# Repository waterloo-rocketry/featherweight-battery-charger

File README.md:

# featherweight-battery-charger

- add grounds
- when your chip suddenly draws a lot of power, it gets a big change in current which is a problem: in those moments, voltage is irregular. so the point of decoupling capacitor is to store charge
- in general, depends on pin/chip, datasheet will give recommended or calculate it yourself :(
- change resistor value (?)
- buck converter -> 12v to 5v (do this cuz it's step down standard), we probably need to design it (we gotta buy buck converter ic maybe check with ash)

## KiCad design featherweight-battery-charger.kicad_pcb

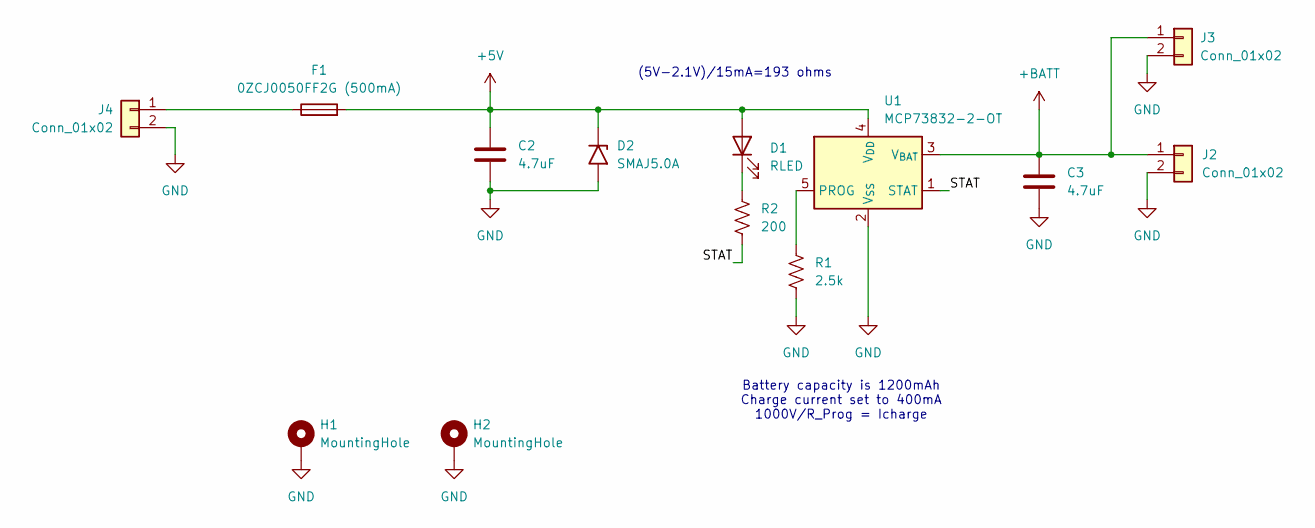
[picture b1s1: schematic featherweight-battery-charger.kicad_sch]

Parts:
C2, C3: 4.7uF; C_0603_1608Metric_Pad1.08x0.95mm_HandSolder
D1: RLED; LED_1206_3216Metric_Pad1.42x1.75mm_HandSolder
D2: SMAJ5.0A; D_SMA
F1: 0ZCJ0050FF2G (500mA); Fuse_1206_3216Metric_Pad1.42x1.75mm_HandSolder
H1, H2: MountingHole; MountingHole_3.2mm_M3_Pad
J2, J3: Conn_01x02; JST_PH_S2B-PH-K_1x02_P2.00mm_Horizontal
J4: Conn_01x02; JST_VH_S2P-VH_1x02_P3.96mm_Horizontal
R1: 2.5k; R_0603_1608Metric_Pad0.98x0.95mm_HandSolder
R2: 200; R_0603_1608Metric_Pad0.98x0.95mm_HandSolder
U1: MCP73832-2-OT; SOT-23-5

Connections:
+5V: C2.1, D1.2 (A), D2.1 (A1), F1.2, U1.4 (V_{DD})
+BATT: C3.1, J2.1, J3.1, U1.3 (V_{BAT})
/STAT: R2.2, U1.1 (STAT)
GND: C2.2, C3.2, D2.2 (A2), H1.1, H2.1, J2.2, J3.2, J4.2, R1.2, U1.2 (V_{SS})
unnamed: D1.1 (K), R2.1
unnamed: F1.1, J4.1
unnamed: R1.1, U1.5 (PROG)

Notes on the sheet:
Battery capacity is 1200mAh Charge current set to 400mA 1000V/R_Prog = Icharge
(5V-2.1V)/15mA=193 ohms

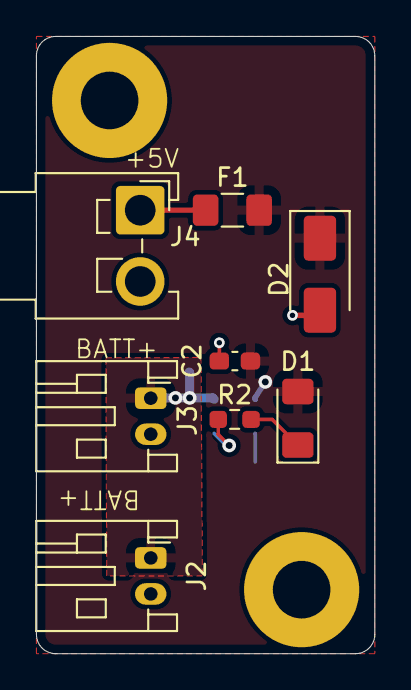
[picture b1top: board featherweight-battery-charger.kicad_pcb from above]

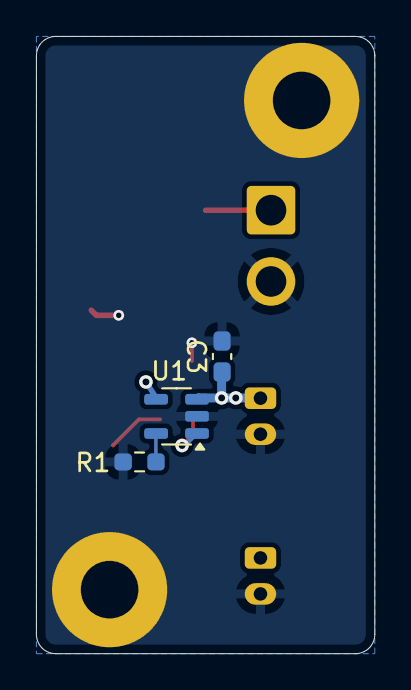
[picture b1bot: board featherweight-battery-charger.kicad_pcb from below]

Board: 2 copper layers, 18.8 x 34.3 mm, 13 parts (3 on the bottom side), 7 nets.

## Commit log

2025-10-27 page setup and team footprints
2025-10-28 Added components + general layout
2025-11-02 updated schematic
2025-11-08 buck converter without values
2025-11-08 Changed resistor icon in schematic
2025-11-24 finished buck converter part
2025-12-01 Added resistor values
2026-01-07 Changed Buck, Added Connectors and Fuse
2026-01-07 To create a diff between PR and main
2026-01-09 Added New Buck and Kicad Footprints Submodule
2026-01-09 Started Layout and Routing
2026-01-10 Did most of the layout and routing, need to finish silkscreen and then check everything
2026-01-10 Fixed some routing and silkscreen, should be done hopefully
2026-01-10 Forgot the schematic changes
2026-01-11 Changed Layout and Routing
2026-01-11 Fixed up Silkscreen
2026-01-16 Remove seemingly pointless via
2026-01-16 Change C2 from 1uF to 4.7uF
2026-01-22 Fixed Dimensions to Line Holes up with Featherweight
2026-01-22 Changed Layout and Routing, Added Calculation Comments and Batt plane for heat diff. Fuse changed to 1206
